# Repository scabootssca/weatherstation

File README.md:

Needs Src/shared/config.h made with this format:

# config.h
```
#ifndef _CONFIG_H_
#define _CONFIG_H_

#define SERVER_IP_ADDRESS "XXX.XXX.XXX.XXX"
#define SERVER_PORT 80
#define MY_IP XXX, XXX, XXX, XXX
#define GATEWAY_IP XXX, XXX, XXX, XXX
#define SUBNET_MASK XXX, XXX, XXX, XXX
#define WIFI_SSID "XXXXXXXXXXX"
#define WIFI_PASS "*******************"
#define GMT_OFFSET XX (-X or just X in hours)
#define ESP_ATMEGA_BAUD_RATE 4800

#endif
```

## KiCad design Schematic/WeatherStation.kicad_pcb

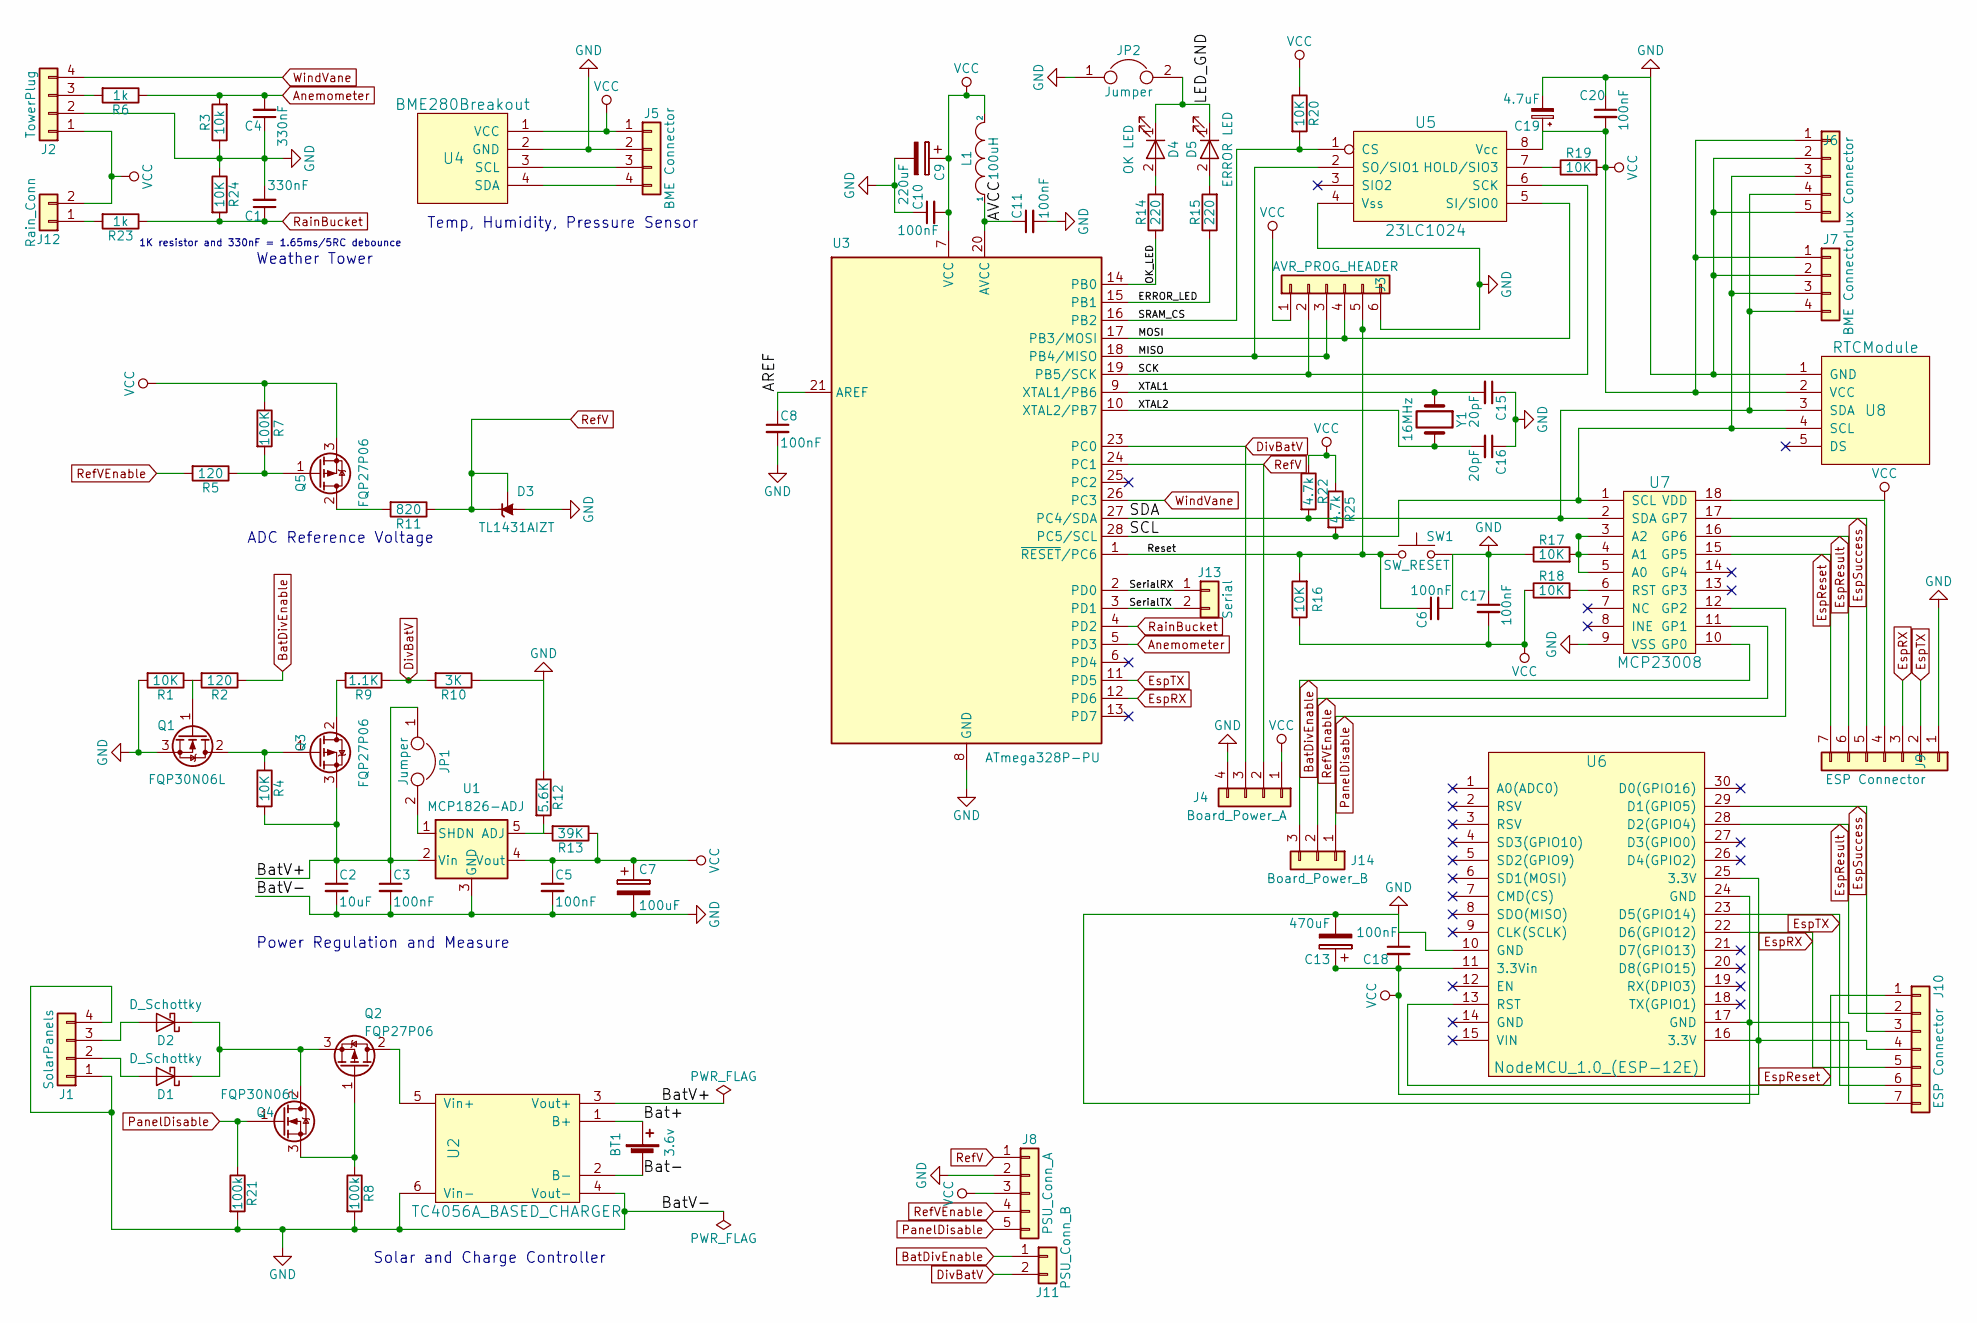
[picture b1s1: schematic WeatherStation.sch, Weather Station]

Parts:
BT1: 3.6v; Keystone_1042_1x18650
C1, C4: 330nF; CP_Radial_D5.0mm_P2.50mm
C2: 10uF; C_Disc_D5.1mm_W3.2mm_P5.00mm
C3, C5, C6, C8, C10, C11, C17, C18, C20: 100nF; C_Disc_D5.0mm_W2.5mm_P5.00mm
C7: 100uF; CP_Radial_D5.0mm_P2.50mm
C9: 220uF; CP_Radial_D6.3mm_P2.50mm
C13: 470uF; CP_Radial_D8.0mm_P2.50mm
C15, C16: 20pF; C_Disc_D5.0mm_W2.5mm_P5.00mm
C19: 4.7uF; CP_Radial_D4.0mm_P2.00mm
D1, D2: D_Schottky; D_DO-15_P12.70mm_Horizontal
D3: TL1431AIZT; TO-92_Inline_Wide
D4: OK LED; LED_D5.0mm
D5: ERROR LED; LED_D5.0mm
J1: SolarPanels; JST_XH_B04B-XH-A_04x2.50mm_Straight
J2: TowerPlug; JST_XH_B04B-XH-A_04x2.50mm_Straight
J3: AVR_PROG_HEADER; Pin_Header_Straight_1x06_Pitch2.54mm
J4: Board_Power_A; JST_XH_B04B-XH-A_04x2.54mm_Straight
J5, J7: BME Connector; JST_XH_B04B-XH-A_04x2.50mm_Straight
J6: Lux Connector; JST_XH_B04B-XH-A_04x2.50mm_Straight
J8: PSU_Conn_A; JST_XH_B05B-XH-A_05x2.50mm_Straight
J9, J10: ESP Connector; JST_XH_B06B-XH-A_07x2.50mm_Straight
J11: PSU_Conn_B; JST_XH_B02B-XH-A_02x2.50mm_Straight
J12: Rain_Conn; JST_XH_B02B-XH-A_02x2.50mm_Straight
J13: Serial; Pin_Header_Straight_1x02_Pitch2.54mm
J14: Board_Power_B; JST_XH_B03B-XH-A_03x2.50mm_Straight
JP1, JP2: Jumper; Pin_Header_Straight_1x02_Pitch2.54mm
L1: 100uH; L_Axial_L5.3mm_D2.2mm_P7.62mm_Horizontal_Vishay_IM-1
Q1, Q4: FQP30N06L; TO-220-3_Vertical
Q2, Q3, Q5: FQP27P06; TO-220-3_Vertical
R1, R4, R16, R17, R18, R19, R20, R24: 10K; R_Axial_DIN0207_L6.3mm_D2.5mm_P7.62mm_Horizontal
R2, R5: 120; R_Axial_DIN0207_L6.3mm_D2.5mm_P7.62mm_Horizontal
R3: 10k; R_Axial_DIN0207_L6.3mm_D2.5mm_P7.62mm_Horizontal
R6, R23: 1k; R_Axial_DIN0207_L6.3mm_D2.5mm_P7.62mm_Horizontal
R7: 100K; R_Axial_DIN0207_L6.3mm_D2.5mm_P7.62mm_Horizontal
R8: 100k; R_Axial_DIN0204_L3.6mm_D1.6mm_P7.62mm_Horizontal
R9: 1.1K; R_Axial_DIN0207_L6.3mm_D2.5mm_P7.62mm_Horizontal
R10: 3K; R_Axial_DIN0207_L6.3mm_D2.5mm_P7.62mm_Horizontal
R11: 820; R_Axial_DIN0207_L6.3mm_D2.5mm_P7.62mm_Horizontal
R12: 5.6K; R_Axial_DIN0207_L6.3mm_D2.5mm_P7.62mm_Horizontal
R13: 39K; R_Axial_DIN0207_L6.3mm_D2.5mm_P7.62mm_Horizontal
R14, R15: 220; R_Axial_DIN0207_L6.3mm_D2.5mm_P7.62mm_Horizontal
R21: 100k; R_Axial_DIN0207_L6.3mm_D2.5mm_P7.62mm_Horizontal
R22, R25: 4.7k; R_Axial_DIN0207_L6.3mm_D2.5mm_P7.62mm_Horizontal
SW1: SW_RESET; SW_PUSH_6mm
U1: MCP1826-ADJ; TO-247-5_Vertical
U2: TC4056A_BASED_CHARGER; TC4056_BREAKOUT
U3: ATmega328P-PU; DIP-28_W7.62mm_Socket
U4: BME280Breakout; Pin_Header_Straight_1x04_Pitch2.54mm
U5: 23LC1024; DIP-8_W7.62mm_Socket
U6: NodeMCU_1.0_(ESP-12E); ESP8266_NODEMCU
U7: MCP23008; DIP-18_W7.62mm
U8: RTCModule; Pin_Header_Straight_1x05_Pitch2.54mm
Y1: 16MHz; Crystal_HC52-8mm_Vertical

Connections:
/AREF: C8.1, U3.21 (AREF)
/AVCC: C11.1, L1.1, U3.20 (AVCC)
/Bat+: BT1.1 (+), U2.1 (B+)
/Bat-: BT1.2 (-), U2.2 (B-)
/BatV+: C2.1, C3.1, JP1.1, Q3.3 (S), R4.2, U1.2 (Vin), U2.3 (Vout+)
/ERROR_LED: R15.1, U3.15 (PB1)
/LED_GND: D4.1 (K), D5.1 (K), JP2.2
/MISO: J3.3, U3.18 (PB4/MISO), U5.2 (SO/SIO1)
/MOSI: J3.4, U3.17 (PB3/MOSI), U5.5 (SI/SIO0)
/OK_LED: R14.1, U3.14 (PB0)
/Reset: C6.1, J3.5, R16.2, SW1.1, U3.1 (~RESET~/PC6)
/SCK: J3.2, U3.19 (PB5/SCK), U5.6 (SCK)
/SCL: J6.3, J7.3, R25.2, U3.28 (PC5/SCL), U7.1 (SCL), U8.4 (SCL)
/SDA: J6.4, J7.4, R22.2, U3.27 (PC4/SDA), U7.2 (SDA), U8.3 (SDA)
/SRAM_CS: R20.2, U3.16 (PB2), U5.1 (CS)
/SerialRX: J13.1, U3.2 (PD0)
/SerialTX: J13.2, U3.3 (PD1)
/XTAL1: C15.2, U3.9 (XTAL1/PB6), Y1.1
/XTAL2: C16.2, U3.10 (XTAL2/PB7), Y1.2
Anemometer: C4.2, R3.2, R6.1, U3.5 (PD3)
BatDivEnable: J11.1, J14.3, R2.1, U7.10 (GP0)
DivBatV: J4.3, J11.2, R9.1, R10.2, U3.23 (PC0)
EspRX: J9.3, J10.5, U3.12 (PD6), U6.22 (D6(GPIO12))
EspReset: J9.7, J10.1, U6.13 (RST), U7.15 (GP5)
EspResult: J9.6, J10.2, U6.28 (D2(GPIO4)), U7.16 (GP6)
EspSuccess: J9.5, J10.3, U6.29 (D1(GPIO5)), U7.17 (GP7)
EspTX: J9.2, J10.6, U3.11 (PD5), U6.23 (D5(GPIO14))
GND: C1.2, C2.2, C3.2, C4.1, C5.2, C6.2, C7.2, C8.2, C9.2, C10.1, C11.2, C13.2, C15.1, C16.1, C17.1, C18.1, C19.2, C20.1, D3.2 (A), J1.1, J1.4, J2.2, J3.6, J4.4, J5.2, J6.2, J6.5, J7.2, J8.2, J9.1, J10.7, JP2.1, Q1.3 (S), R1.2, R3.1, R8.2, R10.1, R12.1, R17.1, R21.2, R24.1, SW1.2, U1.3 (GND), U2.4 (Vout-), U2.6 (Vin-), U3.8 (GND), U3.22 (GND), U4.2 (GND), U5.4 (Vss), U6.10 (GND), U6.17 (GND), U6.24 (GND), U7.9 (VSS), U8.1 (GND)
unnamed: D1.1 (K), D2.1 (K), Q2.3 (S), Q4.2 (D)
unnamed: D1.2 (A), J1.2
unnamed: D2.2 (A), J1.3
unnamed: D4.2 (A), R14.2
unnamed: D5.2 (A), R15.2
unnamed: J2.3, R6.2
unnamed: J5.3, U4.3 (SCL)
unnamed: J5.4, U4.4 (SDA)
unnamed: J12.1, R23.2
unnamed: JP1.2, U1.1 (SHDN)
unnamed: Q1.1 (G), R1.1, R2.2
unnamed: Q1.2 (D), Q3.1 (G), R4.1
unnamed: Q2.1 (G), Q4.3 (S), R8.1
unnamed: Q2.2 (D), U2.5 (Vin+)
unnamed: Q3.2 (D), R9.2
unnamed: Q5.1 (G), R5.1, R7.2
unnamed: Q5.2 (D), R11.2
unnamed: R12.2, R13.2, U1.5 (ADJ)
unnamed: R17.2, U7.3 (A2), U7.4 (A1), U7.5 (A0)
unnamed: R18.2, U7.6 (RST)
unnamed: R19.1, U5.7 (HOLD/SIO3)
PanelDisable: J8.5, J14.1, Q4.1 (G), R21.1, U7.12 (GP2)
RainBucket: C1.1, R23.1, R24.2, U3.4 (PD2)
RefV: D3.1 (REF), D3.3 (K), J4.2, J8.1, R11.1, U3.24 (PC1)
RefVEnable: J8.4, J14.2, R5.2, U7.11 (GP1)
VCC: C5.1, C7.1, C9.1, C10.2, C13.1, C17.2, C18.2, C19.1, C20.2, J2.1, J3.1, J4.1, J5.1, J6.1, J7.1, J8.3, J9.4, J10.4, J12.2, L1.2, Q5.3 (S), R7.1, R13.1, R16.1, R18.1, R19.2, R20.1, R22.1, R25.1, U1.4 (Vout), U3.7 (VCC), U4.1 (VCC), U5.8 (Vcc), U6.11 (3.3Vin), U6.16 (3.3V), U6.25 (3.3V), U7.18 (VDD), U8.2 (VCC)
WindVane: J2.4, U3.26 (PC3)

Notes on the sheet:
Power Regulation and Measure
ADC Reference Voltage
Solar and Charge Controller
Weather Tower
Temp, Humidity, Pressure Sensor
1K resistor and 330nF = 1.65ms/5RC debounce

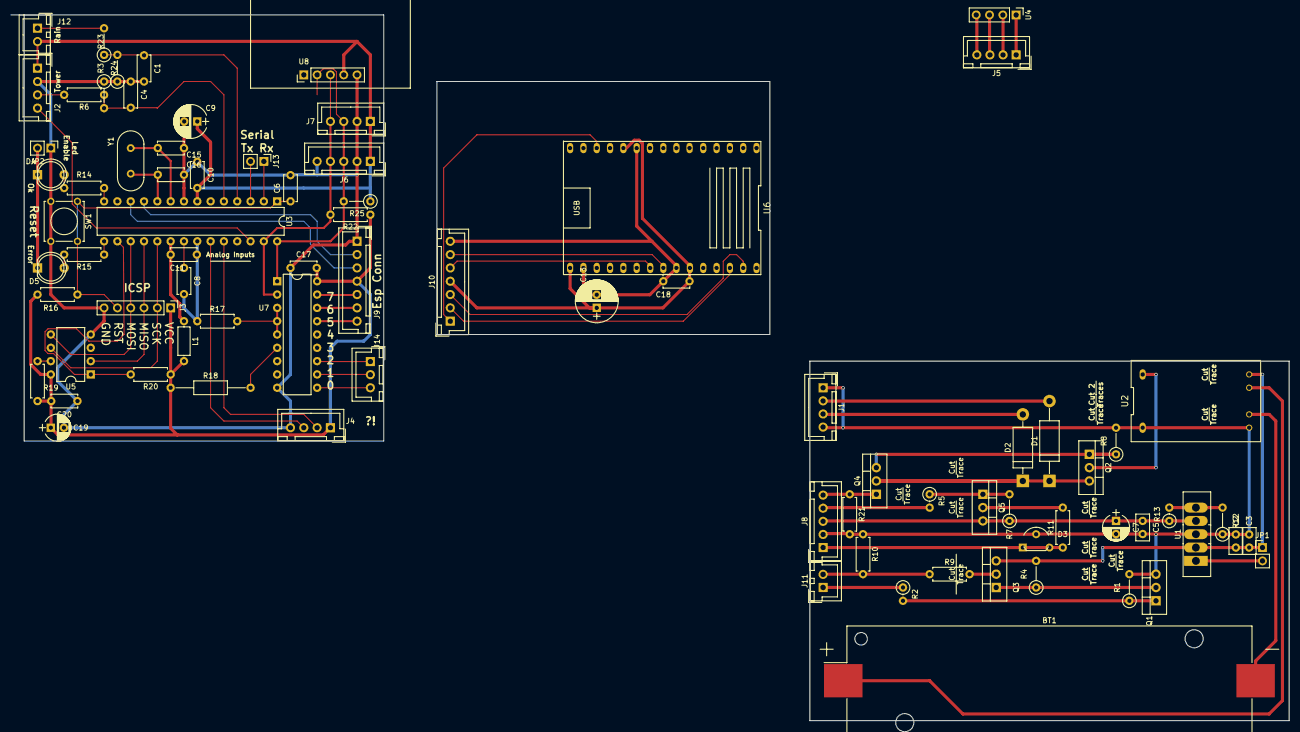
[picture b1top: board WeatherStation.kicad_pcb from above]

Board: 2 copper layers, 243.8 x 134.6 mm, 81 parts (0 on the bottom side), 55 nets.

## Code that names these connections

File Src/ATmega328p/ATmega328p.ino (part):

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
// Pins
// Port B
#define OK_LED_PIN 8     // PB0
#define ERROR_LED_PIN 9  // PB1
#define SRAM_CS_PIN 10   // PB2
#define MOSI_PIN 11      // PB3
#define MISO_PIN 12      // PB4
#define SCK_PIN 13       // PB5

// Port C
#define BAT_ADC_PIN A0       // PC0
#define REF_ADC_PIN A1       // PC1
#define WIND_VANE_ADC_PIN A3 // PC2
// PC3
#define I2C_SDA_PIN A4       // PC4
#define I2C_SCL_PIN A5       // PC5

// Port D
#define RAIN_BUCKET_PIN 2    // PD2
#define ANEMOMETER_PIN 3     // PD3
#define DEBUG_PIN 4          // PD4
#define ESP_TX_PIN 5         // PD5
#define ESP_RX_PIN 6         // PD6


// Mcp23008 pins
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  DEBUG_PRINTLN("1."); // Esp Serial DONE

  // Indicator LEDS
  pinMode(OK_LED_PIN, OUTPUT);
  pinMode(ERROR_LED_PIN, OUTPUT);
  digitalWrite(OK_LED_PIN, HIGH);
  digitalWrite(ERROR_LED_PIN, HIGH);

  // Battery pins
  pinMode(BAT_ADC_PIN, INPUT);
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  debugMode = digitalRead(DEBUG_PIN);

  // Interrupts
  pinMode(ANEMOMETER_PIN, INPUT);
  digitalWrite(ANEMOMETER_PIN, LOW);
  attachInterrupt(digitalPinToInterrupt(ANEMOMETER_PIN), anemometerISR, RISING);

  pinMode(RAIN_BUCKET_PIN, INPUT);
  digitalWrite(RAIN_BUCKET_PIN, LOW);
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
  // SRAM init
  DEBUG_PRINTLN(F("Start SRAM"));
  sram_init(SRAM_CS_PIN); // Will set pin mode and such
  delay(1);

  bool restoredSram = false;
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
  esp_send_debug_request(bootMessage);

  digitalWrite(OK_LED_PIN, LOW);
  digitalWrite(ERROR_LED_PIN, LOW);

  DEBUG_PRINTLN(F("Finished Init"));
  DEBUG_PRINTLN();
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
  #if DEBUG
  if (debugMode) {
    digitalWrite(OK_LED_PIN, HIGH);
    DEBUG2_PRINTLN();
    DEBUG2_PRINT(F("--(Taking sample: "));
    DEBUG2_PRINT(sampleAccumulator.numSamples+1);
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    DEBUG2_PRINTLN();
    #endif

    digitalWrite(OK_LED_PIN, LOW);
  }
  #endif
}
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
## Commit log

2017-09-23 Added .gitignore with .db file and __pycache__
2017-09-24 Added ESP8266 Sketch Code .ino
2017-09-24 Added gitignore for login.h
2017-09-24 Changed from char* in ram to #define to save resources
2017-09-24 Added Parts List Spreadsheet
2017-09-24 Restructuring
2017-09-27 Fixed datapoint selection algorithm cause it was terrible is smarter now. Added current info header and degree symbols instead of *
2017-09-27 Something
2017-09-27 Different?
2017-09-27 Test file; will be removed later probably
2017-10-03 Before Refactor
2017-10-03 Updating to lastest and greatest
2017-10-11 Added new files
2017-10-20 Added led PWM; changed server ip
2017-10-20 Added server/out.htm
2017-10-20 Removed out.htm
2017-10-24 added anemometer and changed digitalWrite to analogWrite for leds since they werent turning off
2017-10-24 Added new php server code
2017-10-26 Removed cruft and using different DHT11 library
2017-10-26 Need these now cause different DHT22 module
2017-10-26 Need these for the draggable slider
2017-10-26 Fixes to server side code
2017-10-26 Removed old server code; added readme
2017-10-29 No more delay() also debug symbols
2017-10-29 Faster moving average SQL query; theme changes
2017-12-12 Removed heatIndex.h put functions in helpers.h
2017-12-12 For wind vane markings
2017-12-12 Holds the structs and such
2017-12-12 Beginnings of makefile
2017-12-12 Added header for mcp23008 8 bit IO expander. Library is modified to support interrupts.
2017-12-12 Added anemometer calibration data
2017-12-12 For BOM and pricing
2017-12-12 Bunch of changes
2017-12-15 Made the interrupt function use ICACHE_RAM_ATTR for quicker execution to help avoid crashes
2017-12-15 moved get rssi to helpers.h
2017-12-15 copyWeatherReading to do deep copy because was copying be reference maybe?
2017-12-15 missed this in the ICACHE_RAM_ATTR commit
2017-12-15 Anemometer refactoring, made the station submit in mph instead of rpm by using stored calibration data.
2017-12-15 made bmp sleep between readings instead of read constantly
2017-12-15 Wifi and record submission refactoring
2017-12-15 Battery reading refactoring and made more accurate
2017-12-15 different copy method for failed readings
2017-12-15 changed spiHz from 500000 to 900000
2017-12-15 More favorable submission intervals for me
2017-12-15 Removed old for DHT sensor
2017-12-15 Moved ip info to the login.h file
2017-12-15 Stuff
2017-12-22 Added more reference info
2017-12-22 Moved this library here so i could modify it a bit maybe
2017-12-22 Added printWeatherReading function in helpers and made default values for a reading to zero for ease of averaging readings.
2017-12-22 login.h --renamedto--> config.h
2017-12-22 Mass sampling algorithm refactor to comply with noaa guidelines more closely to have more directly comparable readings to other compliant stations.
2017-12-26 Added more reference material
2017-12-26 added zeroWeatherReading function
2017-12-26 rename of sample reading
2017-12-26 Debug message changes, added levels changed messages
2017-12-26 LED control changes
2017-12-26 changed to zeroWeatherReading instead of just settings .populated to false cause that doesn't work when averaging readings or they're offset
2017-12-27 Beginnings of using boshes bme library maybe
2017-12-27 Added beginnings of calibration mode
2017-12-27 Made it used a sampleAccumulator reading instead of one for each sample to save on ram
2017-12-27 Wifi and comment refactoring
2017-12-27 Need this for the sampleAccumulator
2017-12-27 Added bosh bme driver code
2017-12-28 Moved definitions to be less scattered
2017-12-28 Moved battery block to the top of the sensing
2017-12-28 Divider using mcp3008
2017-12-28 Added revised schematic
2017-12-28 I think I finally am doing the battery voltage measurement more or less correct.
2017-12-28 Testing streaming large data through post request
2017-12-28 Upped baud to 115200
2017-12-29 Added beginnings of battery percent approximation
2017-12-29 Should have been in the last commit with battery percent approximation
2017-12-29 Working on being able to stream data that won't fit in ram, pic of sky or maybe large amounts of results?
2017-12-29 Clarifying the text in some print()s
2018-01-13 Initial ESP + ATTINY companion code commit
2018-01-13 Schematic and Reference update
2018-01-14 Working Fast (Enough) Actually slow Communication library
2018-01-14 Working Send and recieve and sleep
2018-01-17 Yup..
2018-01-18 Working attiny sample prototype
2018-01-27 Adding SRAM chip support to retain data across crashes
2018-01-27 Backup and references and crap iterations
2018-01-27 weird?
2018-01-27 Removed this
2018-01-27 Made SRAM work like I want I think
2018-01-27 Made max storage depend on storage size of SRAM
2018-01-27 Print numSamples and numBatterySamples in printWeatherReading
2018-01-27 Stream sending testing
2018-01-30 Initial Commit for ATmega328 controller
2018-01-30 Moved settings around, made esp able to submit to wifi
2018-01-31 Added Esp sleep on command and awake from atmega
2018-01-31 Added uptime printout
2018-01-31 Changed esp IP
2018-01-31 Added pretty print timestamp function
2018-01-31 Made ESP use a static ip
2018-01-31 Rearranged schematic files
2018-01-31 Seperated weather reading structs and helper functions into their own module
2018-02-01 Added Indicator LEDS again and more informative pin map
2018-02-01 Started in ATmega328 SRAM code
2018-02-01 SRAM now restores accumulator
2018-02-01 Made SRAM storage, retrieval work correctly.
2018-02-02 Made battery samples work correctly and solar panel enable/disable
2018-02-02 Didn't need this? Need to fix on a time reference
2018-02-04 Added debug msg
2018-02-04 Added mcp to atmega
2018-02-04 Working (I think) again complete station, hopefully no more crashes
2018-02-05 Cleaning up station from old or unused files
2018-02-05 More cleaning and starting new docs
2018-02-05 more
2018-02-05 Readme typos
2018-02-06 Added server php code
2018-02-09 Moved generate_url to ATmega.ino from weather_readings.h
2018-02-09 DEBUG_PRINT and DEBUG_PRINTLN, only get 1 char per cycle from esp and reference mv to 2500mv
2018-02-09 Enabled WDT
2018-02-09 Use mean of cartesian wind angle coords then back to degrees for accurate average angle instead of just mean of the angles cause 355+10 == ~180 not ~7 like it should
2018-02-09 Check for buffer overflow
2018-02-09 Storing for new wind direction method and removed old comments and added new ones
2018-02-15 Added BH1750 Lux Sensor
2018-02-15 Debug print levels added
2018-02-15 ESP parses response for success and forwards result to atmega
2018-02-15 Made clock sync with offset set by how long it takes to upload
2018-02-15 SRAM layout rearrangements *take use sizeof for the storage of readings and the accumulator *longer populated key *Easy to adjust spi HZ
2018-02-15 ESP debug request support, print and send reset flags to server on restart so we can track and hopefully reduce resets
2018-02-15 Added to gitignore
2018-02-15 Updated lotsa server stuff
2018-02-20 Added esp waking mode
2018-02-20 Bug with esp print, would print u_int8 instead of as char
2018-02-23 Made watchdog to 8 seconds
2018-02-23 Changed types for readings lots of uint64 to uint32 cause 64 was way too big pointless waste. Other type changes like double to float
2018-02-23 Added ram usage debug printout
2018-02-23 Removed unused function
2018-02-23 No upload offset for RTC
2018-02-23 Added timeouts and wdt_resets
2018-02-23 Changed a bunch of prints to shorten and reduce messages to save on ram or flash
2018-02-23 Forgot this in the batteryMv change commit
2018-02-23 Esp submit logic reorder
2018-02-23 Disabled rain pulse detection for now
2018-02-23 Beginnings of debug request code what will store in sram
2018-02-23 Change debug level
2018-02-24 Made the read, write index a uint16_t instead of uint8_t because it could only hold 256 readings instead of the ~3K the ram is capable of
2018-03-05 Redid rain measurement to measure the delta of the pulses instead of counting them per section, should be more accurate hopefully
2018-03-05 Comments
2018-03-05 Added rain back in
2018-03-05 Reference
2018-03-05 Swapped esp serial and request result pins because the new result pins are low on reboot so if the esp crashes then the atmega wont think the esp had a result
2018-03-05 Wind gust
2018-03-05 Added esp RESETTING mode
2018-03-11 Redid a lot trying to stop watchdog timeouts
2018-03-11 Better size defines in sram using sizeof instead of having it hardcoded
2018-03-11 Added = 0 for timestamp instead of leaving the value undefined
2018-03-11 Redid a lot trying to make it stop freezing
2018-03-15 I fell behind
2018-03-20 Made RTC and BME use I2C library instead of Wire, also deleted some unused things so it could still fit in flash
2018-03-20 Made IO expander print the result of the fetch
2018-03-20 Beginnings of error checking for readings
2018-03-20 MIT -> GNU License?!
2018-03-20 Added I2C bus reset on ATMega reboot as per spec
2018-03-20 Beginnings of different time deltas between different reading types
2018-04-16 Updated Schematic
2018-05-14 Changed ESP reset pin to a different pin
2018-05-14 More Comments
2018-05-14 Beginnings of lux sensor disabling on error like bme can
2018-05-14 Made I2C lib print user friendly device name from address on bus errors
2018-05-14 Rain counts were being averaged, should be accumlative instead
2018-05-14 Made esp pull result and success pins low on sleep
2018-05-14 Schematic Updates
2018-05-17 Changed pin assignments to reflect the new
2018-05-17 I2C error handling improvements. Displays Read/Write, # of errors. Resets the i2c bus after 2 errors on it
2018-05-17 Added version and compile time print on station boot
2018-05-17 Longer time for refV to stabilize
2018-05-17 Change esp reset pin to one on mcp23008
2018-05-17 I2C reboot code refresh
2018-05-17 Set reference pin on atmega to be vcc with cap on external pin
2018-05-20 ADC Overhaul for battery v and other readings
2018-05-20 Moved battery reading higher up the sample function to before wind reading
2018-05-20 Added auto version to sketch to be built into rom
2018-06-02 C : : Updated Schemati
2018-06-13 This
2018-06-14 Started bones of simplified esp redo
2018-06-15 Semi working
2018-06-15 Working?
2018-06-15 Reading interval back to 5 mins
2018-06-15 Git version header included again
2018-06-28 Removed old server code while I work on new
2018-06-28 Added back request fail reason submission
2025-11-19 Add lighter selection color with glow effect
    Added ::selection and ::-moz-selection styles with light blue
    background (#a8d4ff) and text-shadow glow for better visual feedback.
2025-11-19 Add comprehensive architecture analysis and PLC automation roadmap
    Document includes:
    - System architecture overview and major functions analysis
    - Identification of 5 critical bugs and 4 security vulnerabilities
    - Performance bottleneck analysis with optimization recommendations
    - Code quality evaluation (readability, maintainability, best practices)
    - Detailed roadmap for Conditional Automation Engine (CAE) feature
2025-11-19 Add Conditional Automation Engine for PLC-like control
    Implements rule-based automation system for greenhouse control:
    - automation_rules.h: Data structures for rules stored in EEPROM
    - automation_engine.h: Rule evaluation with hysteresis and cooldowns
    - Integrates into ATmega328p.ino main firmware
    Features:
    - Support for 8 rules with 2 conditions each

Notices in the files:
Src/ATmega328p/ATmega328p.ino:
Copyright 2017 Jason Ryan Richards
This program is free software: you can redistribute it and/or modify
it under the terms of the GNU General Public License as published by
the Free Software Foundation, either version 3 of the License, or
(at your option) any later version.
